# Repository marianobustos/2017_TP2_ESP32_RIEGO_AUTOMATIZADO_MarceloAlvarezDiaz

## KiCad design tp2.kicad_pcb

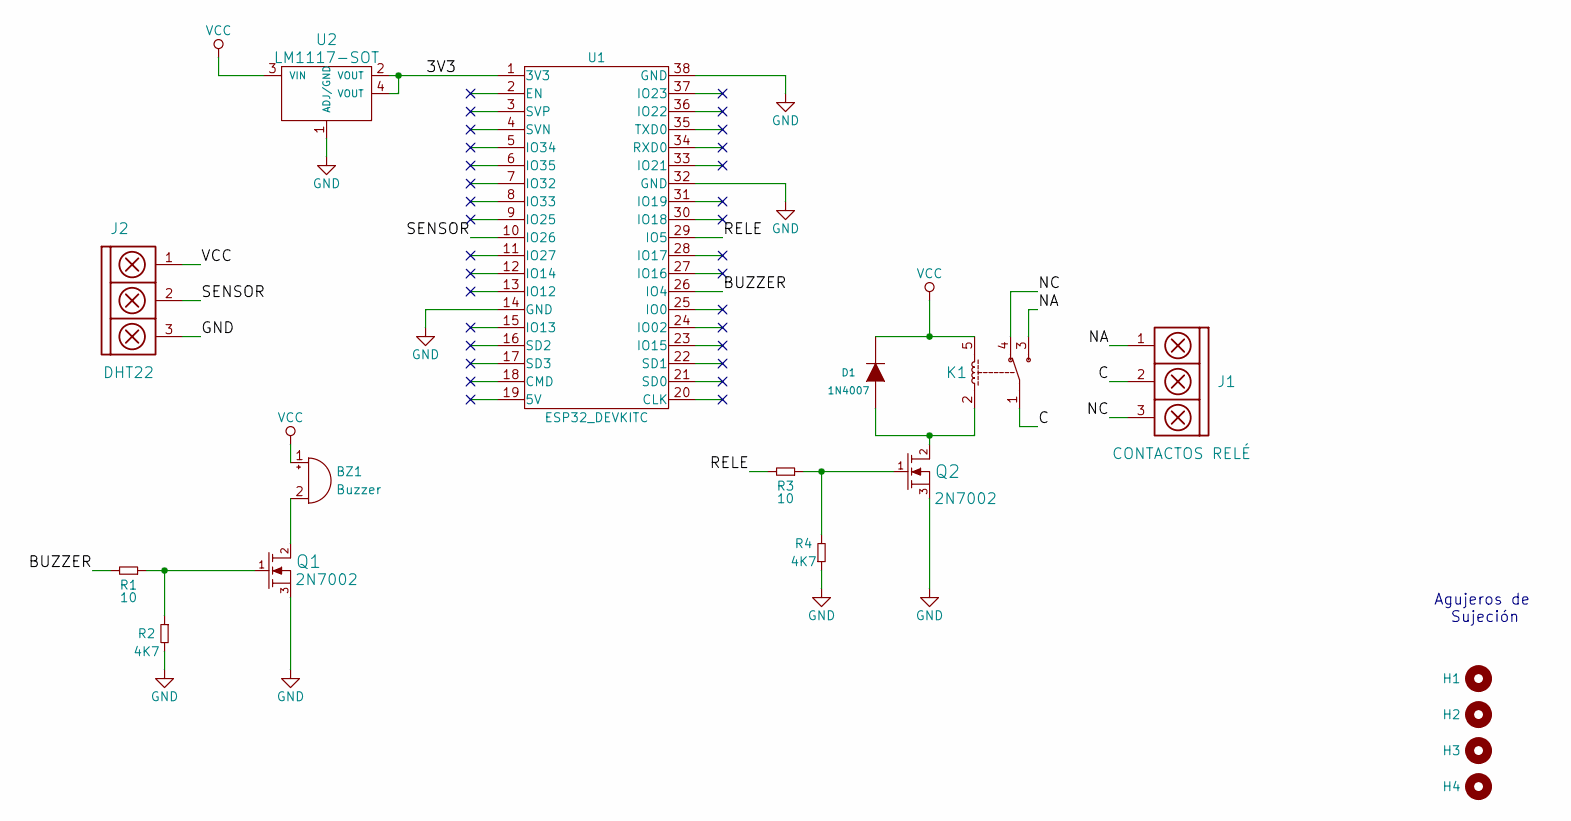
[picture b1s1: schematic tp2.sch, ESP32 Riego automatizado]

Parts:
BZ1: Buzzer; Buzzer_12mm
D1: 1N4007; sod123
H1, H2, H3, H4: Mounting_Hole; Tornillo_M3_8mm
J1: CONTACTOS RELÉ; BORNERA3
J2: DHT22; BORNERA3
K1: RELAY_C; Relay_C
Q1, Q2: 2N7002; SOT23
R1, R3: 10; R_1206
R2, R4: 4K7; R_1206
U1: ESP32_DEVKITC
U2: LM1117-SOT; SOT223

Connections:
/3V3: U1.1 (3V3), U2.2 (VOUT), U2.4 (VOUT)
/BUZZER: R1.2, U1.26 (IO4)
/C: J1.2, K1.1
/NA: J1.1, K1.3
/NC: J1.3, K1.4
/RELE: R3.2, U1.29 (IO5)
/SENSOR: J2.2, U1.10 (IO26)
GND: J2.3, Q1.3 (S), Q2.3 (S), R2.2, R4.1, U1.14 (GND), U1.32 (GND), U1.38 (GND), U2.1 (ADJ/GND)
unnamed: BZ1.2 (+), Q1.2 (D)
unnamed: D1.1 (A), K1.2, Q2.2 (D)
unnamed: Q1.1 (G), R1.1, R2.1
unnamed: Q2.1 (G), R3.1, R4.2
VCC: BZ1.1 (-), D1.2 (K), J2.1, K1.5, U2.3 (VIN)

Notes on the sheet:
Agujeros de Sujeción

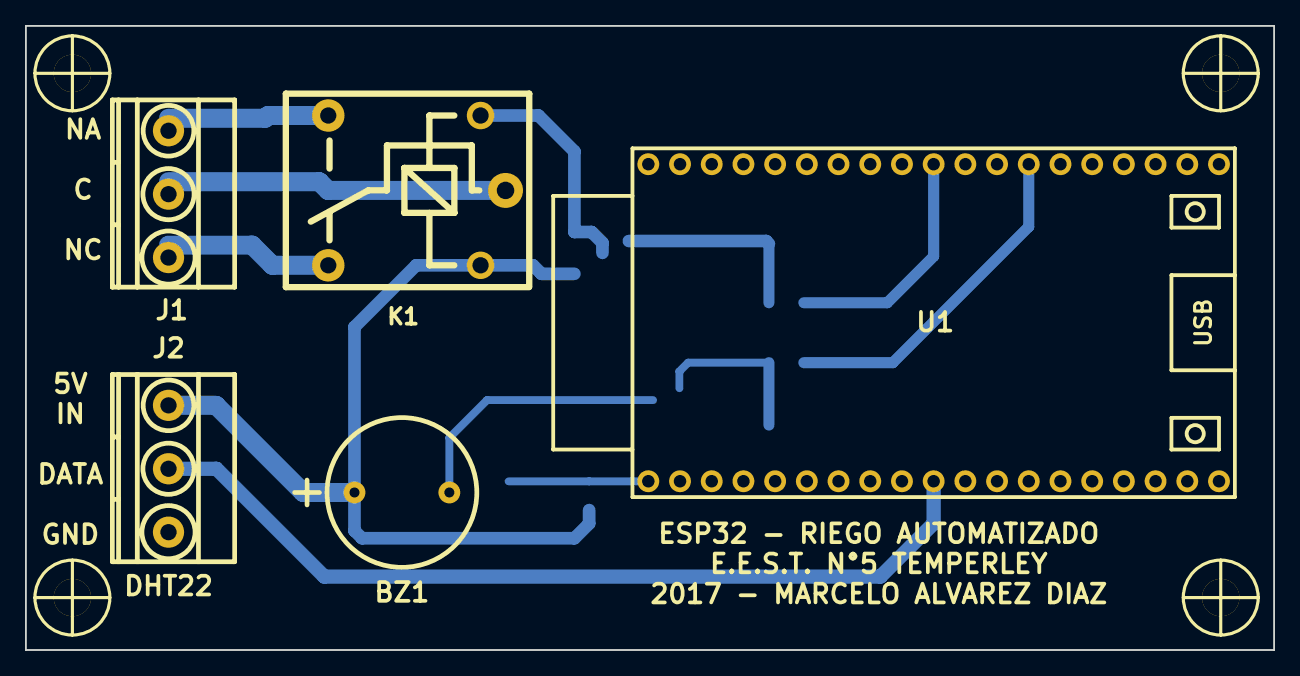
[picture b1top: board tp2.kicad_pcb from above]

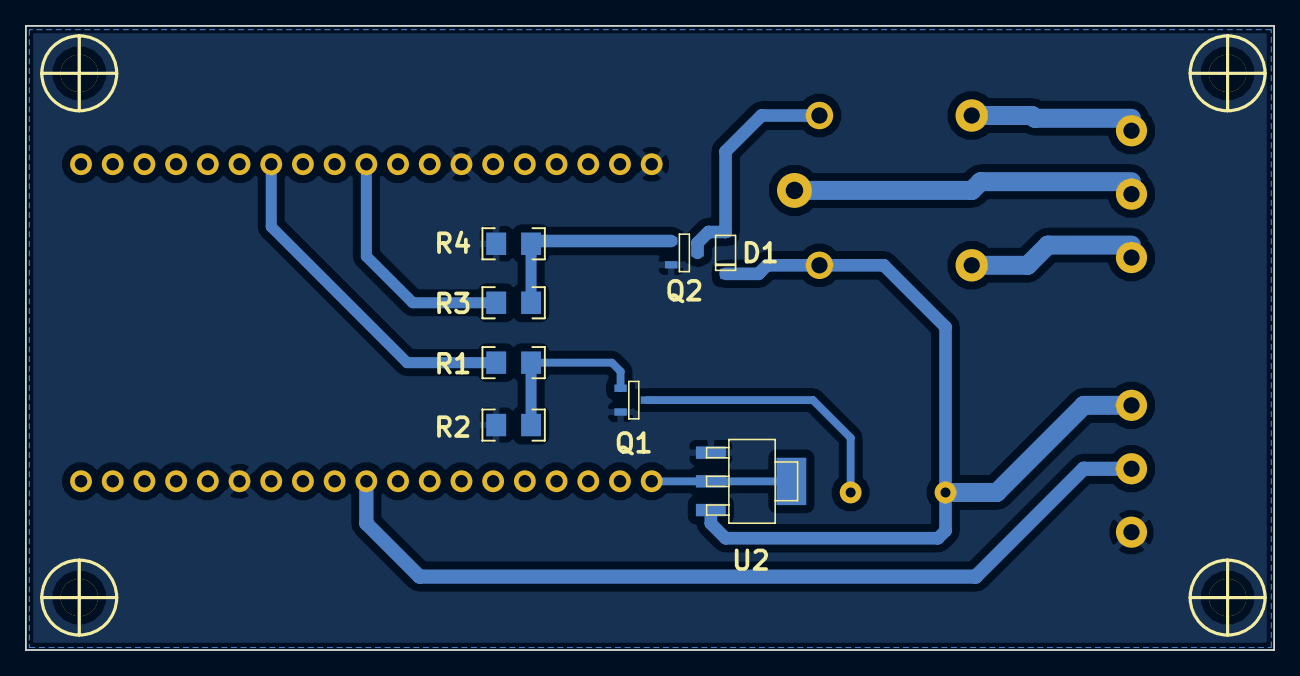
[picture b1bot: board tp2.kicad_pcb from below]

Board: 2 copper layers, 100.0 x 50.0 mm, 17 parts (8 on the bottom side), 13 nets.

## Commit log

2018-03-25 Versión inicial
